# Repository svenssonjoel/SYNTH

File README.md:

# SYNTH
Synthesizer hardware and software experiments

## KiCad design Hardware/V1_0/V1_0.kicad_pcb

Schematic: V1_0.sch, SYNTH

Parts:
C1: 2.2u; C_0603_1608Metric
J1: Micro_SD_Card_Det; microSD_HC_Hirose_DM3D-SF
MK1, MK2, MK3, MK4: Mounting_Hole; MountingHole_3.2mm_M3
R1, R2, R3, R4, R5, R6, R7: 10k; R_0603_1608Metric

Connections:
/SDIO_CK: J1.5 (CLK), R4.1; also elsewhere on the board
/SDIO_CMD: J1.3 (CMD), R5.1; also elsewhere on the board
/SDIO_D0: J1.7 (DAT0), R3.1; also elsewhere on the board
/SDIO_D1: J1.8 (DAT1), R2.1; also elsewhere on the board
/SDIO_D2: J1.1 (DAT2), R7.1; also elsewhere on the board
/SDIO_D3: J1.2 (DAT3/CD), R6.1; also elsewhere on the board
/SDIO_DET: J1.10 (DET_A), R1.1; also elsewhere on the board
GND: C1.2, J1.6 (VSS), J1.9 (DET_B), J1.11 (SHIELD); also elsewhere on the board

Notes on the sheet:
Waveform storage

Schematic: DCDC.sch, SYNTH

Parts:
C2, C5, C6, C7, C8, C10, C30: 2.2u; C_0603_1608Metric
C3: 1u; C_0603_1608Metric
C4: 4.7u; C_0603_1608Metric
C9: 100n; C_0603_1608Metric
C11: 100u; CP_EIA-3528-12_Kemet-T
C29: 100u; CP_Radial_D10.0mm_P5.00mm
L1: 22U; L_Taiyo-Yuden_MD-5050
R8, R14: 10k; R_0603_1608Metric
R9, R11: 249k; R_0603_1608Metric
R10, R12: 91k; R_0603_1608Metric
R13: 33k; R_0603_1608Metric
U1: LM27762; WSON-12-1EP_3x2mm_P0.5mm_EP1x2.65_ThermalVias
U2: REF3030; SOT-23
U3: MCP16311_2; MSOP-8_3x3mm_P0.65mm

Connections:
+5V: C2.1, C5.1, C29.1, R8.1, U1.3 (VIN), U1.8 (EN-), U1.12 (EN+), U3.3 (EN), U3.4 (V_IN); also elsewhere on the board
/RAIL+: C6.1, R11.1, U1.11 (OUT+); also elsewhere on the board
/RAIL-: C7.1, R9.2, R10.1, U1.6 (OUT-); also elsewhere on the board
/VREF: U2.2; also elsewhere on the board
GND: C2.2, C4.2, C5.2, C6.2, C7.2, C8.2, C10.2, C11.2, C29.2, C30.1, R10.2, R12.2, R14.1, U1.4 (GND), U1.13 (PAD), U2.3, U3.5 (P_GND), U3.8 (A_GND); also elsewhere on the board
unnamed: C3.1, U1.10 (C+)
unnamed: C3.2, U1.9 (C-)
unnamed: C4.1, U1.5 (CP)
unnamed: C8.1, U3.2 (VCC)
unnamed: C9.1, U3.7 (BOOST)
unnamed: C9.2, L1.1, U3.6 (SW)
unnamed: R8.2, U1.1 (PGOOD)
unnamed: R9.1, U1.7 (FB-)
unnamed: R11.2, R12.1, U1.2 (FB+)
unnamed: R13.1, R14.2, U3.1 (V_FB)

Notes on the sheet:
1,2× ((249+91)÷91) = 4.48
−1,22×((249+91)÷91) = −4.56
Close to USB port

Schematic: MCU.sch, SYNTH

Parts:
C14, C15, C16, C18, C20, C21, C22: 2.2u; C_0603_1608Metric
C17: 100n; C_0603_1608Metric
C19, C23: 15p; C_0603_1608Metric
D1: RED; LED_0603_1608Metric
D2: GREEN; LED_0603_1608Metric
J2: USART2; JST_PH_B4B-PH-K_1x04_P2.00mm_Vertical
J3: USB_B_Mini; USB_Mini-B_Lumberg_2486_01_Horizontal
J4: UART; JST_PH_B4B-PH-K_1x04_P2.00mm_Vertical
P1: SWD; JST_PH_B6B-PH-K_1x06_P2.00mm_Vertical
R15, R16: 22R; R_0603_1608Metric
R25, R26: 1k; R_0603_1608Metric
RV1, RV2, RV3, RV4: R_POT; Potentiometer_Bourns_PTV09A-2_Single_Horizontal
SW3: BOOT0; SW_SPDT_PCM12
U4: STM32F40X_LQFP64; LQFP-64_10x10mm_P0.5mm
Y1: 8M; Crystal_SMD_5032-4Pin_5.0x3.2mm

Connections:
+5V: J3.1; also elsewhere on the board
/MCU/BOOT0: SW3.2 (B), U4.60 (BOOT0(VPP)); also elsewhere on the board
/MCU/NRST: C17.1, P1.2, U4.7 (NRST); also elsewhere on the board
/MCU/POT1: RV1.2, U4.22 (PA6(ADC12_IN6)); also elsewhere on the board
/MCU/POT2: RV2.2, U4.23 (PA7(ADC12_IN7)); also elsewhere on the board
/MCU/POT3: RV3.2, U4.24 (PC4(ADC12_IN14)); also elsewhere on the board
/MCU/POT4: RV4.2, U4.25 (PC5(ADC12_IN15)); also elsewhere on the board
/MCU/SWCLK: P1.5, U4.49 (PA14(JTCK-SWCLK)); also elsewhere on the board
/MCU/SWDIO: P1.3, U4.46 (PA13(JTMS-SWDIO)); also elsewhere on the board
/MCU/UART_RXD: J4.2, U4.15 (PA1(ADC123_IN1)); also elsewhere on the board
/MCU/UART_TXD: J4.3, U4.14 (PA0(ADC123_IN0/WKUP)); also elsewhere on the board
/MCU/USART2_RX: J2.2, U4.17 (PA3(ADC123_IN3)); also elsewhere on the board
/MCU/USART2_TX: J2.3, U4.16 (PA2(ADC123_IN2)); also elsewhere on the board
/MCU/USB_DM: R16.2, U4.44 (PA11); also elsewhere on the board
/MCU/USB_DP: R15.2, U4.45 (PA12); also elsewhere on the board
/VREF: C14.1, RV1.1, RV2.1, RV3.1, RV4.1, U4.13 (VDDA); also elsewhere on the board
GND: C14.2, C15.1, C16.1, C17.2, C18.2, C19.1, C20.2, C21.2, C22.2, C23.1, D1.1 (K), D2.1 (K), J2.1, J3.5, J3.6, J4.1, P1.4, RV1.3, RV2.3, RV3.3, RV4.3, SW3.1 (A), U4.12 (VSSA), U4.18 (VSS), U4.28 (PB2-BOOT1), U4.63 (VSS), Y1.2, Y1.4; also elsewhere on the board
unnamed 47: C15.2, U4.31 (VCAP1); also elsewhere on the board
unnamed 48: C16.2, U4.47 (VCAP2); also elsewhere on the board
unnamed 49: C19.2, U4.5 (PH0-OSC_IN), Y1.1; also elsewhere on the board
unnamed 50: C23.2, U4.6 (PH1-OSC_OUT), Y1.3; also elsewhere on the board
unnamed: D1.2 (A), R25.2
unnamed: D2.2 (A), R26.2
unnamed: J3.2, R16.1
unnamed: J3.3, R15.1
unnamed 73: R25.1, U4.26 (PB0(ADC12_IN8)); also elsewhere on the board
unnamed 74: R26.1, U4.27 (PB1(ADC12_IN9)); also elsewhere on the board

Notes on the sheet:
Bypass, place next to VDD pins
UART PINS UART4 TX: 14, 51 UART4 RX: 15, 52 UART5 TX: 53 UART5 RX: 54
LQFP64 TIM 2,3,4,5 PWM (TIM1 is more capable than TIM2 - 5 TIM1 CH1 PIN 23 (N), 27(N), 34(N), 36(N), 41 TIM1 CH2 PIN 42 TIM1 CH3 PIN 43 TIM1 CH4 PIN 44 (Maybe prefer these ?) TIM2 CH1 PIN 14, 21 TIM2 CH2 PIN 15, 55 TIM2 CH3 PIN 16, 29 TIM2 CH4 PIN 17, 30 TIM3 CH1 PIN 37, 56 TIM3 CH2 PIN 38 TIM3 CH3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

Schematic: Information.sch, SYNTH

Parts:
C24: 10u; CP_EIA-3216-18_Kemet-A
C25: 0.1u; C_0603_1608Metric
C26, C27, C28: 10uF; C_0805_2012Metric
J5, J6, J7, J8, J9, J10: C; PinHeader_1x02_P2.54mm_Vertical
J11: AUDIO; JST_PH_B2B-PH-K_1x02_P2.00mm_Vertical
J?ee1: AudioJack3_Ground; Jack_3.5mm_CUI_SJ-3524-SMT_Horizontal
R17, R18, R20, R22, R24: 10k; R_0603_1608Metric
R19, R21, R23: 30k; R_0603_1608Metric
U5: AD5330; TSSOP-20_4.4x6.5mm_P0.65mm
U6: LF356; SOIC-8_3.9x4.9mm_P1.27mm

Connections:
/BUF_0: U5.1 (BUF); also elsewhere on the board
/DAC1: C27.2; also elsewhere on the board
/DAC2: C28.2; also elsewhere on the board
/DACS/DACOUT: C26.2, U5.4 (VOUT)
/DB0: U5.13 (DB0); also elsewhere on the board
/DB1: U5.14 (DB1); also elsewhere on the board
/DB2: U5.15 (DB2); also elsewhere on the board
/DB3: U5.16 (DB3); also elsewhere on the board
/DB4: U5.17 (DB4); also elsewhere on the board
/DB5: U5.18 (DB5); also elsewhere on the board
/DB6: U5.19 (DB6); also elsewhere on the board
/DB7: U5.20 (DB7); also elsewhere on the board
/N_CLR_0: U5.9 (N_CLR); also elsewhere on the board
/N_LDAC_0: U5.10 (N_LDAC); also elsewhere on the board
/N_WR_0: U5.7 (N_WR); also elsewhere on the board
/RAIL+: U6.7; also elsewhere on the board
/RAIL-: U6.4; also elsewhere on the board
/VREF: U5.3 (VREF); also elsewhere on the board
GND: C24.2, C25.2, J11.2, J?ee1.G, J?ee1.S, U5.5 (GND), U5.6 (N_CS), U5.8 (GAIN), U6.3; also elsewhere on the board
unnamed: C26.1, J5.1, J8.1
unnamed: C27.1, J6.1, J9.1
unnamed: C28.1, J7.1, J10.1
unnamed: J5.2, R19.2
unnamed: J6.2, R21.2
unnamed: J7.2, R23.2
unnamed: J8.2, R18.1
unnamed: J9.2, R20.1
unnamed: J10.2, R22.1
unnamed: J11.1, J?ee1.R, J?ee1.T, R24.1, U6.6
unnamed: R17.2, U5.11 (N_PD)
unnamed: R18.2, R19.1, R20.2, R21.1, R22.2, R23.1, R24.2, U6.2

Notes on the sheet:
Line level
http://dangerousprototypes.com/blog/2010/03/29/play-wav-audio-files-with-ad5330-and-arduino/

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
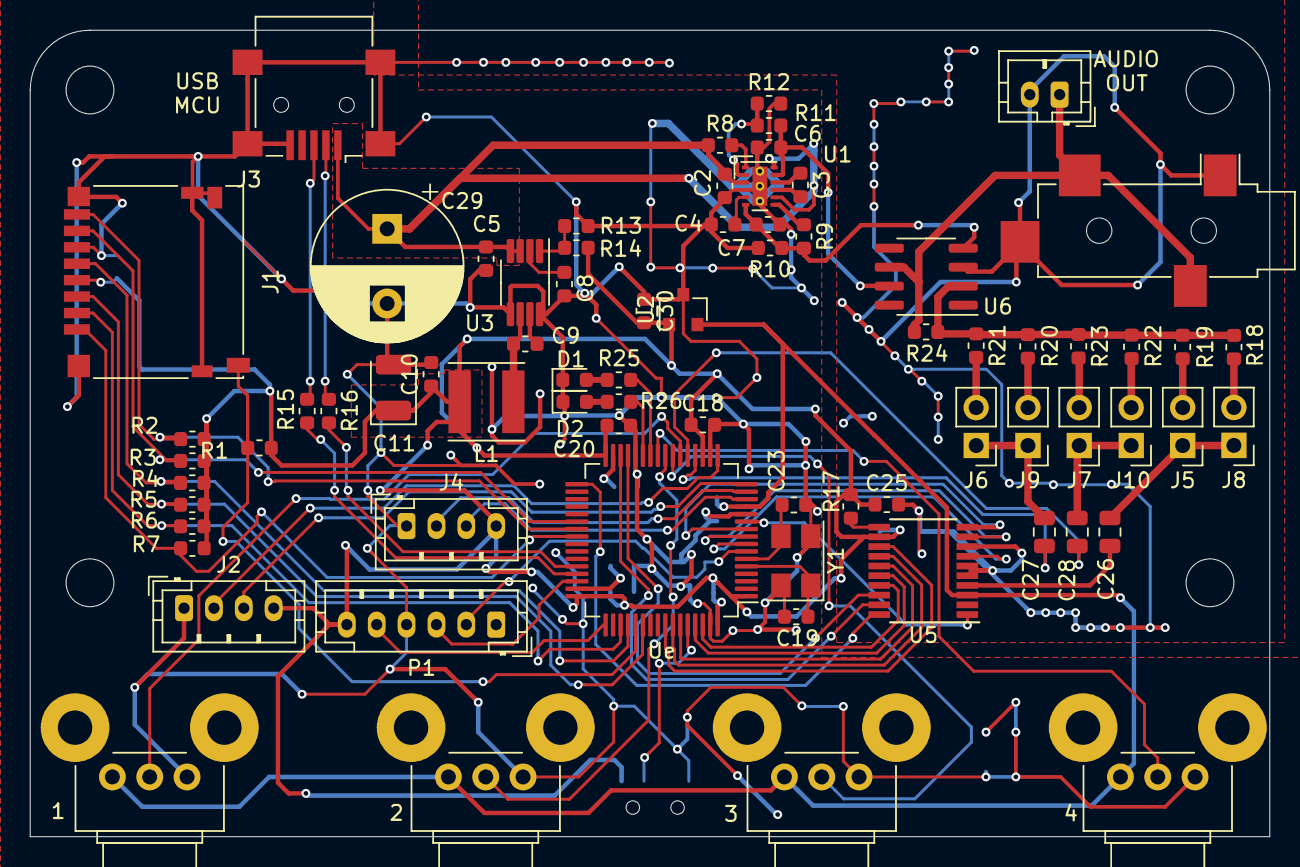
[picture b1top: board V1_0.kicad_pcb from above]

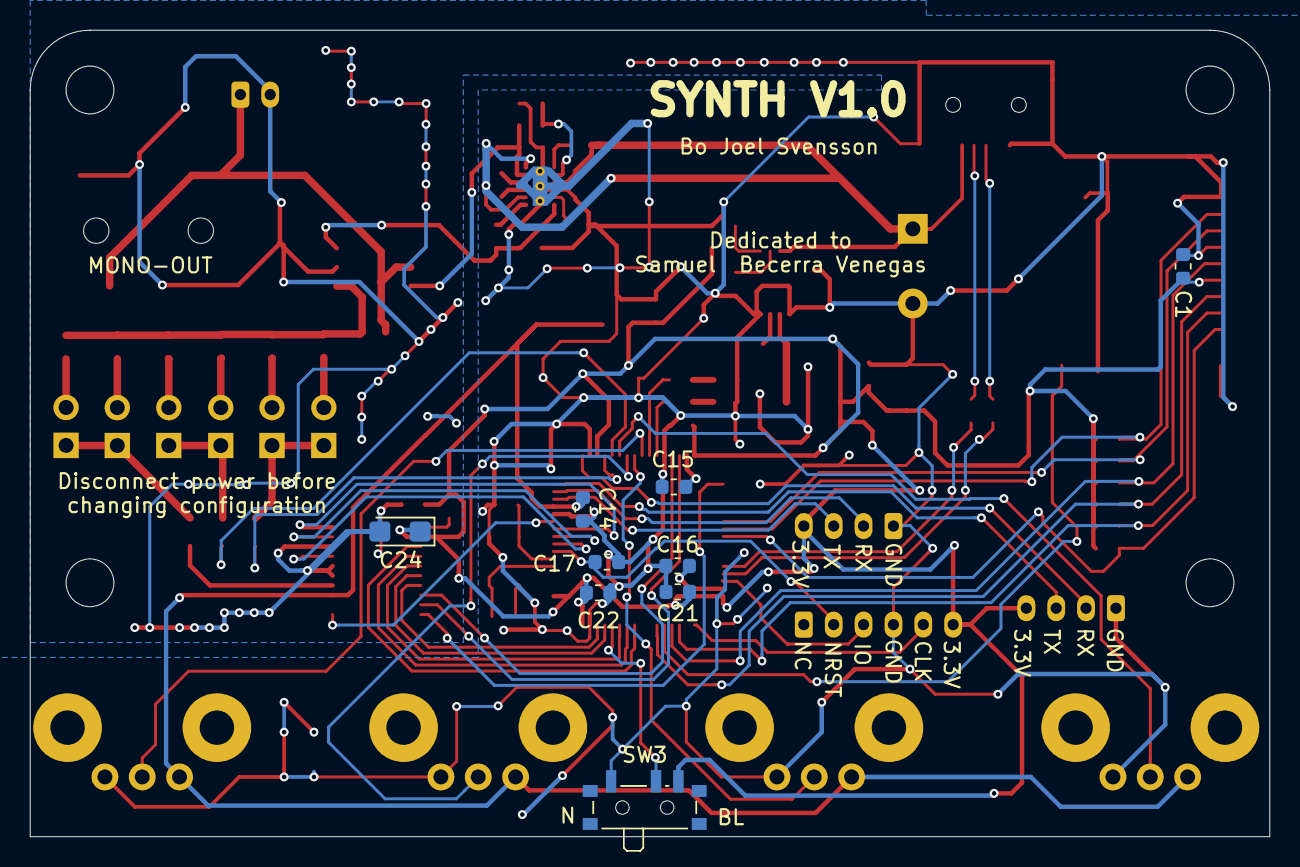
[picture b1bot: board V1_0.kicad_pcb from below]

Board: 2 copper layers, 83.0 x 54.0 mm, 86 parts (9 on the bottom side), 74 nets.

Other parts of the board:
Ue: STM32F40X_LQFP64; LQFP-64_10x10mm_P0.5mm

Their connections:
/BUF_0: Ue.11; also elsewhere on the board
/DAC1: Ue.20; also elsewhere on the board
/DAC2: Ue.21; also elsewhere on the board
/DB0: Ue.57; also elsewhere on the board
/DB1: Ue.58; also elsewhere on the board
/DB2: Ue.59; also elsewhere on the board
/DB3: Ue.61; also elsewhere on the board
/DB4: Ue.62; also elsewhere on the board
/DB5: Ue.29; also elsewhere on the board
/DB6: Ue.30; also elsewhere on the board
/DB7: Ue.33; also elsewhere on the board
/MCU/BOOT0: Ue.60; also elsewhere on the board
/MCU/NRST: Ue.7; also elsewhere on the board
/MCU/POT1: Ue.22; also elsewhere on the board
/MCU/POT2: Ue.23; also elsewhere on the board
/MCU/POT3: Ue.24; also elsewhere on the board
/MCU/POT4: Ue.25; also elsewhere on the board
/MCU/SWCLK: Ue.49; also elsewhere on the board
/MCU/SWDIO: Ue.46; also elsewhere on the board
/MCU/UART_RXD: Ue.15; also elsewhere on the board
/MCU/UART_TXD: Ue.14; also elsewhere on the board
/MCU/USART2_RX: Ue.17; also elsewhere on the board
/MCU/USART2_TX: Ue.16; also elsewhere on the board
/MCU/USB_DM: Ue.44; also elsewhere on the board
/MCU/USB_DP: Ue.45; also elsewhere on the board
/N_CLR_0: Ue.9; also elsewhere on the board
/N_LDAC_0: Ue.10; also elsewhere on the board
/N_WR_0: Ue.8; also elsewhere on the board
/SDIO_CK: Ue.52; also elsewhere on the board
/SDIO_CMD: Ue.54; also elsewhere on the board
/SDIO_D0: Ue.38; also elsewhere on the board
/SDIO_D1: Ue.39; also elsewhere on the board
/SDIO_D2: Ue.40; also elsewhere on the board
/SDIO_D3: Ue.51; also elsewhere on the board
/SDIO_DET: Ue.53; also elsewhere on the board
/VREF: Ue.13; also elsewhere on the board
GND: Ue.12, Ue.18, Ue.28, Ue.63; also elsewhere on the board
unnamed 47: Ue.31; also elsewhere on the board
unnamed 48: Ue.47; also elsewhere on the board
unnamed 49: Ue.5; also elsewhere on the board
unnamed 50: Ue.6; also elsewhere on the board
unnamed 73: Ue.26; also elsewhere on the board
unnamed 74: Ue.27; also elsewhere on the board

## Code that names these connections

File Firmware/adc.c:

/*
    Copyright 2019/2020   Joel Svensson	svenssonjoel@yahoo.se
                          Anders Thorsén thorsenanders@yahoo.com


    This program is free software: you can redistribute it and/or modify
    it under the terms of the GNU General Public License as published by
    the Free Software Foundation, either version 3 of the License, or
    (at your option) any later version.

    This program is distributed in the hope that it will be useful,
    but WITHOUT ANY WARRANTY; without even the implied warranty of
    MERCHANTABILITY or FITNESS FOR A PARTICULAR PURPOSE.  See the
    GNU General Public License for more details.

    You should have received a copy of the GNU General Public License
    along with this program.  If not, see <http://www.gnu.org/licenses/>.
*/

#include "adc.h"


/* 
   IN 6    (PA6)
   IN 7    (PA7)
   IN 14   (PC4)
   IN 15   (PC5) 

 */

#define NUM_CH 4
#define NUM_SAMPLES 1

static adcsample_t sample_buff[NUM_CH * NUM_SAMPLES];

static const ADCConversionGroup ADC_conversion_group = {
  FALSE,                                /*NOT CIRCULAR*/
  NUM_CH,                               /*NUMB OF CHANNELS*/
  NULL,                                 /*NO ADC CALLBACK*/
  NULL,                                 /*NO ADC ERROR CALLBACK*/
  0,                                    /* CR1 */
  ADC_CR2_SWSTART,                      /* CR2 */
  ADC_SMPR1_SMP_AN14(ADC_SAMPLE_3) |
  ADC_SMPR1_SMP_AN15(ADC_SAMPLE_3),     /* SMPR1 */
  ADC_SMPR2_SMP_AN6(ADC_SAMPLE_3) |
  ADC_SMPR2_SMP_AN7(ADC_SAMPLE_3) ,     /* SMPR2 */
  0,                                    /* HTR */
  0,                                    /* LTR */
  0,                                    /* SQR1 */
  0,                                    /* SQR2 */
  ADC_SQR3_SQ1_N(ADC_CHANNEL_IN6) | 
  ADC_SQR3_SQ2_N(ADC_CHANNEL_IN7) |
  ADC_SQR3_SQ3_N(ADC_CHANNEL_IN14) |
  ADC_SQR3_SQ4_N(ADC_CHANNEL_IN15)    /* SQR3 */
  
};


/*===========================================================================*/
/*  ADC thread                                                              */
/*===========================================================================*/

#define ADC_WA_SIZE 2048

static THD_FUNCTION(ADCThread, arg) {
  (void) arg;

  while(TRUE) {
    adcConvert(&ADCD1, &ADC_conversion_group, sample_buff, NUM_SAMPLES);
    chThdSleepMilliseconds(500);
  }
}


void adc_init(void) {

  palSetPadMode(GPIOA, 6, PAL_MODE_INPUT_ANALOG);
  palSetPadMode(GPIOA, 7, PAL_MODE_INPUT_ANALOG);
  palSetPadMode(GPIOC, 4, PAL_MODE_INPUT_ANALOG);
  palSetPadMode(GPIOC, 5, PAL_MODE_INPUT_ANALOG);

  adcStart(&ADCD1, NULL);

  chThdCreateFromHeap(NULL, ADC_WA_SIZE, "ADC", NORMALPRIO + 1, ADCThread, NULL);
}

uint16_t adc_value(int ix) {
  if (ix < 0 || ix >= 4) return 0;
  return (int16_t)sample_buff[ix];
}

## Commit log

2019-12-27 added spice simulation project
2019-12-30 added files to repo
2019-12-30 some work on the MCU part
2019-12-30 tweaks
2019-12-31 low energy work
2020-01-07 experimenting
2020-01-07 silks
2020-01-07 added stp file
2020-01-07 added some ordernr
2020-01-07 lots of tweaks
2020-01-09 hacking
2020-01-09 GERBER
2020-01-29 bugfixing in progress
2020-01-29 I found a bug
2020-04-13 adding Firmware with ADC experiment
2020-04-13 tweaks to FW
2020-04-13 experiments
2020-04-16 small tweaks to bug fixed version of synth pcb. Also converted to kicad 5.1.5
2020-05-04 tweak
2020-05-10 tweak fab layers
